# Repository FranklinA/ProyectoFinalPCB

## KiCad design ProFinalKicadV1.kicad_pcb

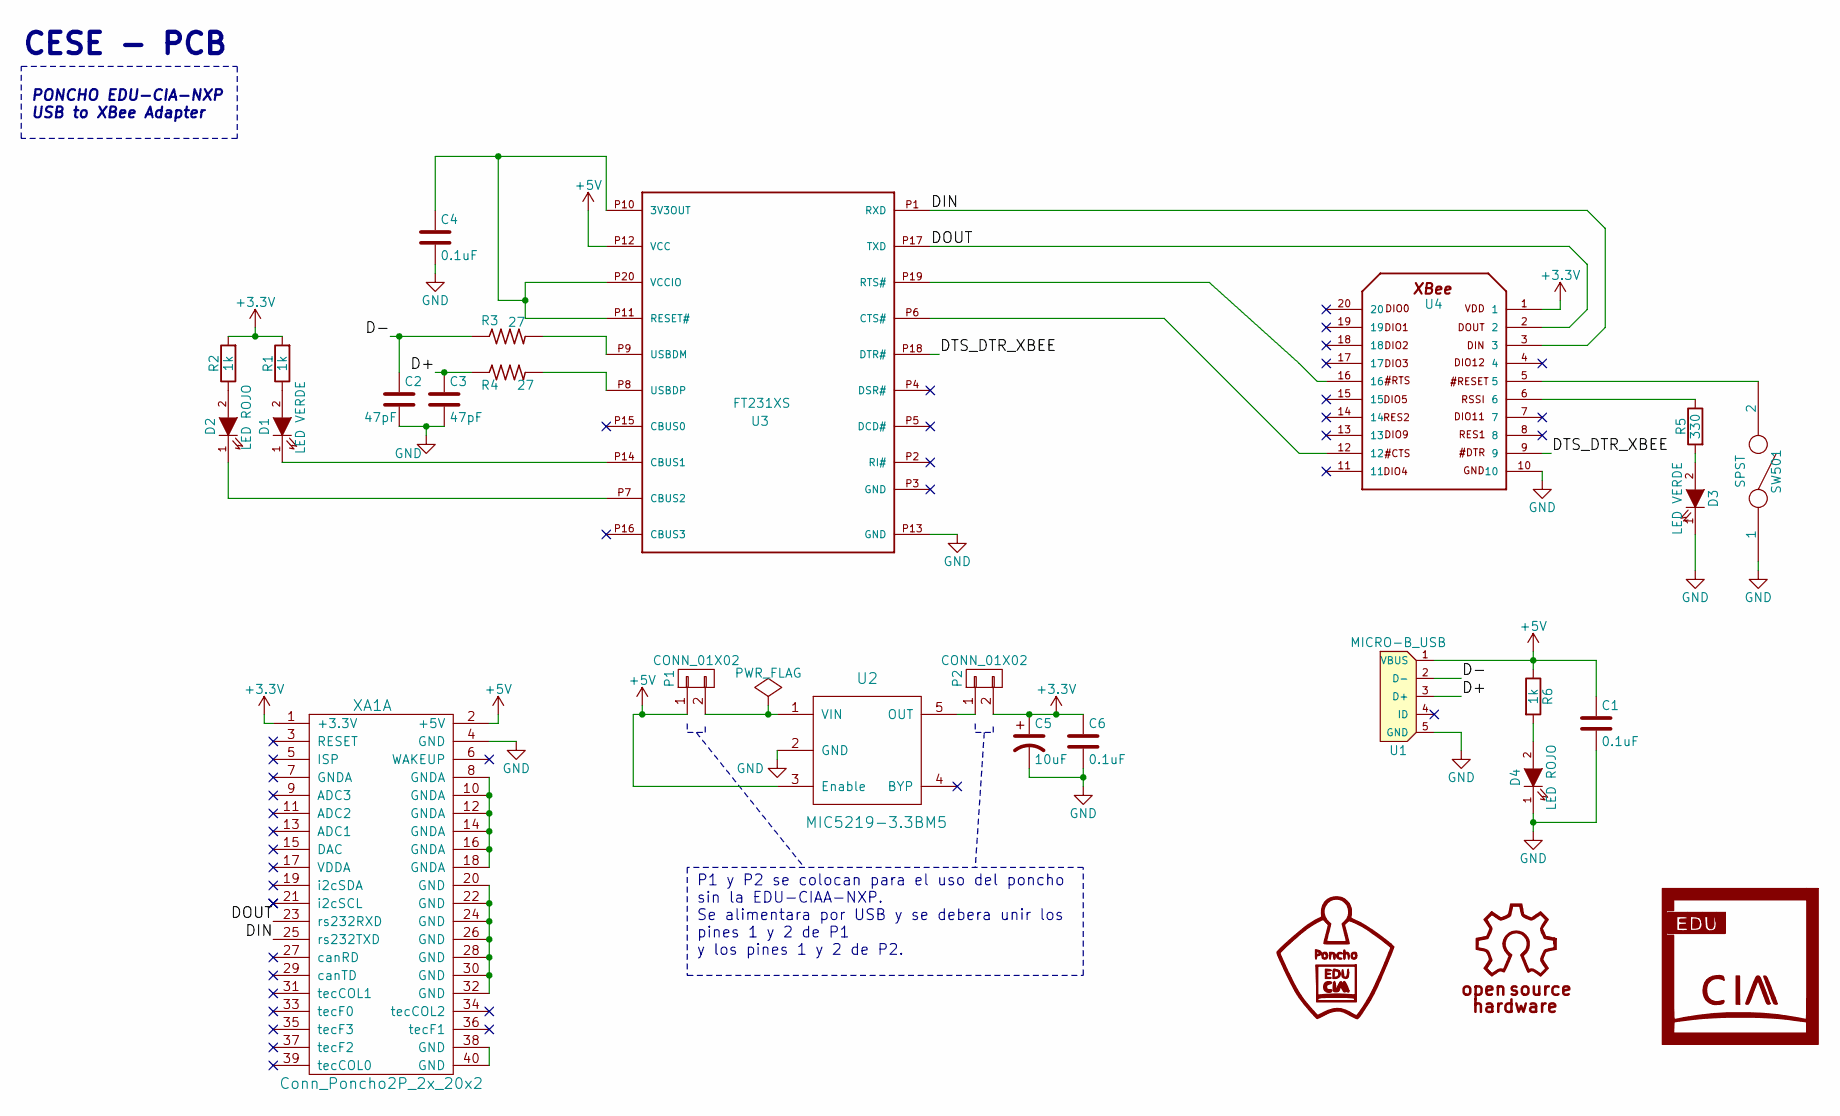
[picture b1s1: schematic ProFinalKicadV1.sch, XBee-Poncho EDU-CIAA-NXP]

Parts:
C1: 0.1uF; C_0603_HandSoldering; Digikey# MCT0603-1.00K-CFTR-ND
C2, C3: 47pF; C_0603_HandSoldering; Digikey# 445-1277-1-ND
C4, C6: 0.1uF; C_0603_HandSoldering; Digikey# 311-1343-1-ND
C5: 10uF; CP_4x5mm; Digikey# 493-14027-2-ND
D1, D3: LED VERDE; LED_0603_HandSoldering; Digikey# 475-2920-1-ND
D2, D4: LED ROJO; LED_0603_HandSoldering; Digikey# 475-2512-1-ND
P1, P2: CONN_01X02; pin_strip_2mm_2; Digikey# 952-1938-ND
R1, R2, R6: 1k; R_0603_HandSoldering; Digikey# MCT0603-1.00K-CFTR-ND
R3, R4: 27; r_0603; Digikey# P27GCT-ND
R5: 330; R_0603_HandSoldering; Digikey# RMCF0603JT330RCT-ND
SW501: SPST; smd_push; Digikey# 952-1938-ND
U1: MICRO-B_USB; conn_usb_B_micro_smd; Digikey# 732-2734-ND
U2: MIC5219-3.3BM5; sot23-5; Digikey# MIC5219-3.3BM5-TR-ND
U3: FT231XS; qfn-20; Digikey# 768-1128-2-ND
U4: XB24-Z7WIT-004; XBee; Digikey# 602-1098-ND
XA1: Conn_Poncho2P_2x_20x2; Conn_Poncho_Derecha; Digikey# 952-1938-ND

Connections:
+3V3: C5.1, C6.1, P2.2, R1.2, R2.2, U4.1, XA1.1 (+3.3V)
+5V: C1.1, P1.1, R6.1, U1.1 (VBUS), U2.3 (Enable), U3.P12 (VCC), XA1.2 (+5V)
/D+: C3.1, R4.1, U1.3 (D+)
/D-: C2.1, R3.1, U1.2 (D-)
/DIN: U3.P1 (RXD), U4.3, XA1.25 (rs232TXD)
/DOUT: U3.P17 (TXD), U4.2, XA1.23 (rs232RXD)
/DTS_DTR_XBEE: U3.P18 (DTR#), U4.9
GND: C1.2, C2.2, C3.2, C4.2, C5.2, C6.2, D3.1 (K), D4.1 (K), SW501.1, U1.5 (GND), U2.2 (GND), U3.P13 (GND), U4.10, XA1.4 (GND)
unnamed: C4.1, U3.P10 (3V3OUT), U3.P11 (RESET#), U3.P20 (VCCIO)
unnamed: D1.1 (K), U3.P14 (CBUS1)
unnamed: D1.2 (A), R1.1
unnamed: D2.1 (K), U3.P7 (CBUS2)
unnamed: D2.2 (A), R2.1
unnamed: D3.2 (A), R5.2
unnamed: D4.2 (A), R6.2
unnamed: P1.2, U2.1 (VIN)
unnamed: P2.1, U2.5 (OUT)
unnamed: R3.2, U3.P9 (USBDM)
unnamed: R4.2, U3.P8 (USBDP)
unnamed: R5.1, U4.6
unnamed: SW501.2, U4.5
unnamed: U3.P6 (CTS#), U4.12
unnamed: U3.P19 (RTS#), U4.16
unnamed: XA1.8 (GNDA), XA1.10 (GNDA), XA1.12 (GNDA), XA1.14 (GNDA), XA1.16 (GNDA), XA1.18 (GNDA)
unnamed: XA1.20 (GND), XA1.22 (GND), XA1.24 (GND), XA1.26 (GND), XA1.28 (GND), XA1.30 (GND), XA1.32 (GND)
unnamed: XA1.38 (GND), XA1.40 (GND)

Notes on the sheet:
CESE - PCB
PONCHO EDU-CIA-NXP USB to XBee Adapter
P1 y P2 se colocan para el uso del poncho sin la EDU-CIAA-NXP. Se alimentara por USB y se debera unir los pines 1 y 2 de P1 y los pines 1 y 2 de P2.

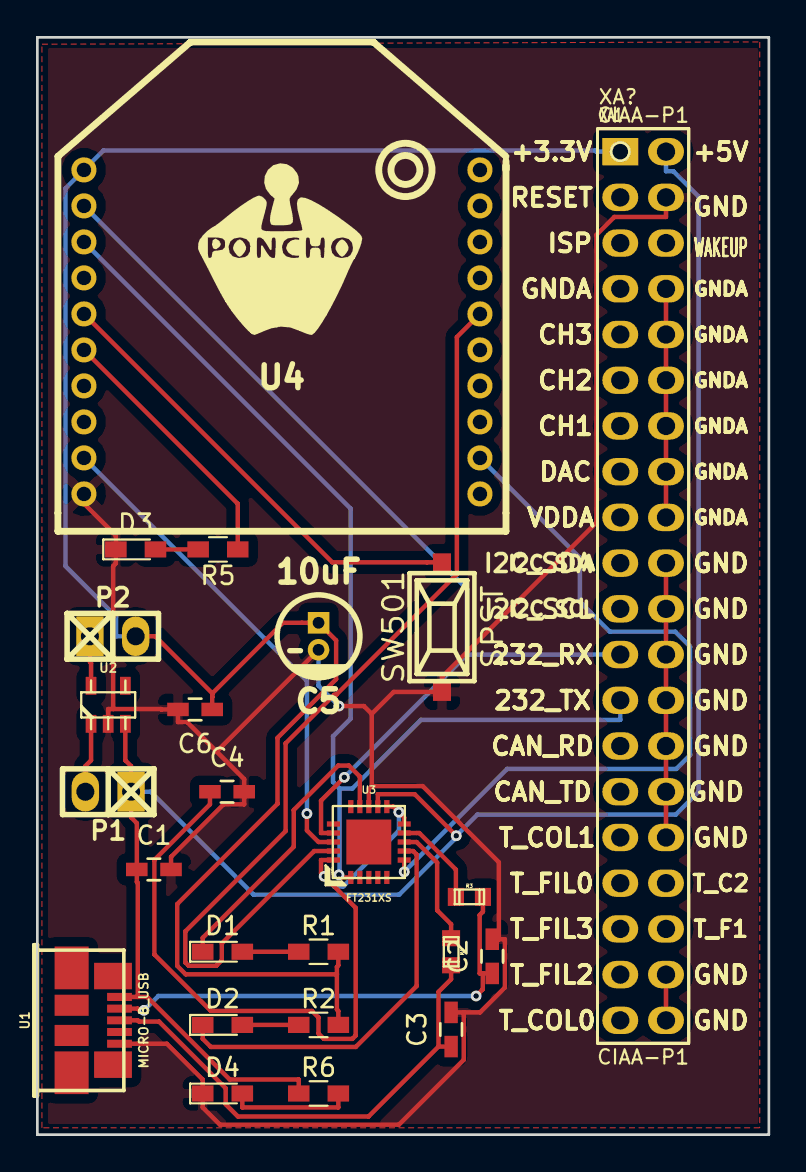
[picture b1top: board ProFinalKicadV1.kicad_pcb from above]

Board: 2 copper layers, 40.6 x 61.0 mm, 25 parts (0 on the bottom side), 26 nets.

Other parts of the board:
XA?: Plantilla_Poncho_Derecha

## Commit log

2017-07-27 Actualización Repo Proyecto Final PCB
    Version 1.3
2017-08-05 Actualización Rev.1.3
    Antes del cambio de repositorio.
2017-08-05 Actualizando Esquematico Rev 1.3 y campos Kicost
    Actualizando Esquematico en base a a la Rev 1.3 y campos Kicost
    faltantes
2017-08-05 Doc inicial de proyecto
    Ante proyecto.
2017-08-11 Asociando 3D
    3D de elementos previo a ruteo de PCB
2017-08-11 Poncho 3D y xbee 3D
    Podrá ser un pin_strip_20x2-90.wrl o un pin_strip_20x2.wrl según
    configuración de pistas. Al final se define su estructura 3D. Se estima
    colocar dos sockets de 8 y sacar el trafico de Xbee para no confundir
    en al visión del diseño
2017-08-11 PCB
    Ruteo de la placa
2017-08-11 Relleno Zona GND
    Relleno GND
2017-08-11 Imagen para el repositorio
    Adjunto imagen para mejorar la presentación en el repositorio
2017-08-11 Modificación por imagen del readme
    agrego imagen mejorada para presentación del repositorio
2017-08-11 Modificación 2 readme
    por incluir imagen
2017-08-11 modificación rearme imagen correcta
    Imagen correcta
2017-08-11 Ultima modificación
    Ultima modificación para el .md
2017-08-11 Actualización 33Ohm
    Actualización de la resistencia de 330 Ohm para el usos de Kicost
2017-08-12 Actualización para modelo 3D en cualquier PC
    Actualización para modelo 3D en cualquier PC que descarga el proyecto
2017-08-12 Mejora 3D para R3 y R4
    Mejora para 3D de R3 y R4 en cualquier PC que descargue el proyecto.
2017-08-12 Modelo 3D V.1
    Se carga nuevamente para descargar en cualquier pc y visualizar
    correctamente todos los elementos del integrado
